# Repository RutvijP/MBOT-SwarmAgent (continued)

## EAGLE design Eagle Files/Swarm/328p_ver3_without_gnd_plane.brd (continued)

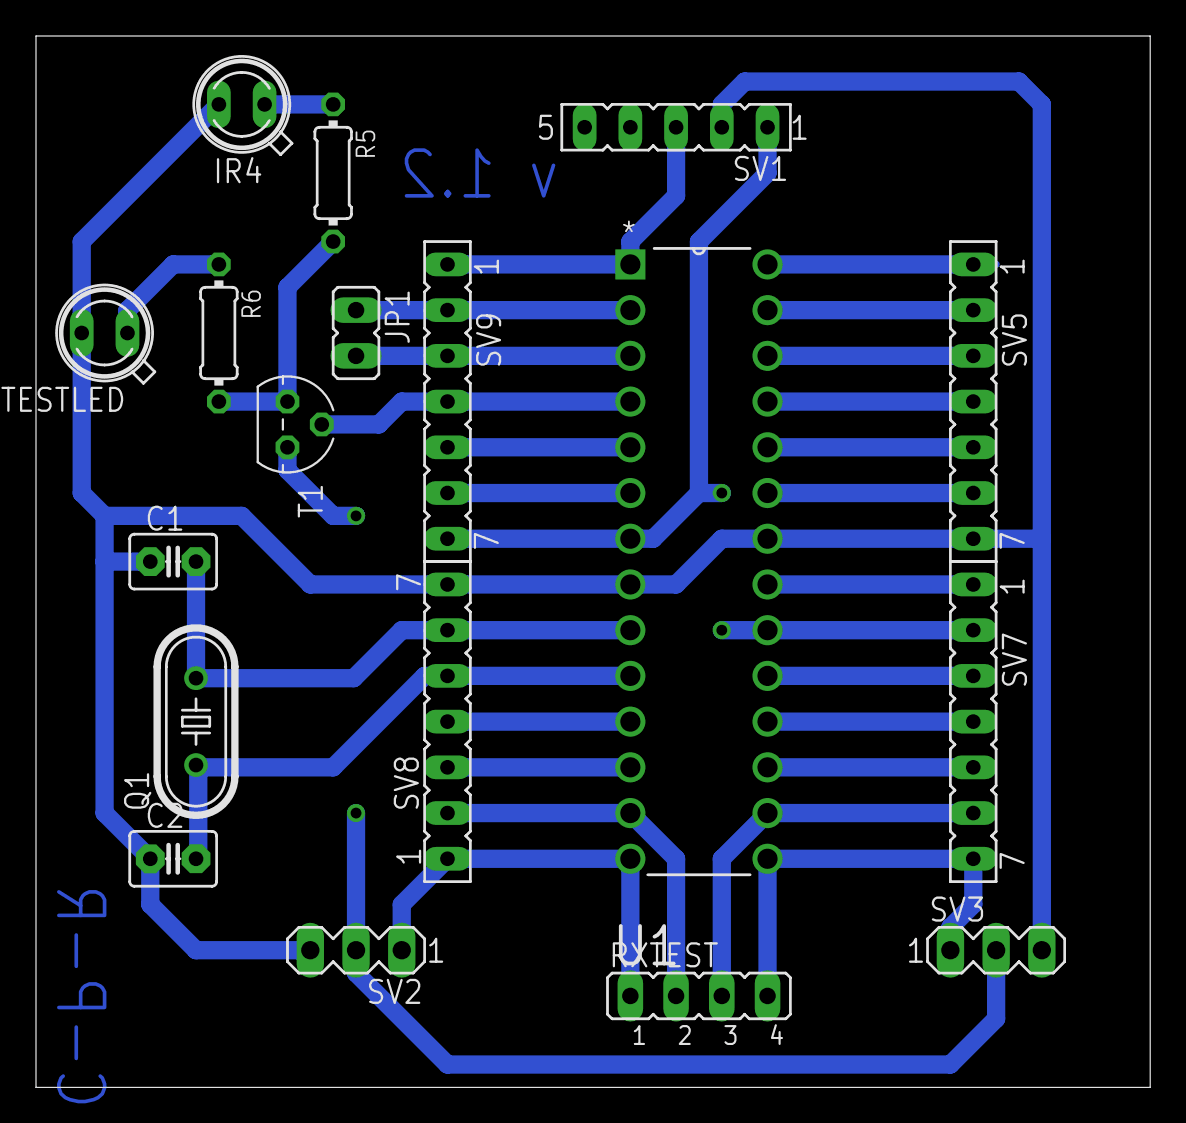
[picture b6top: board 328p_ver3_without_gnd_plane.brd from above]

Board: 2 copper layers, 61.9 x 58.4 mm, 18 parts (0 on the bottom side), 30 nets.
